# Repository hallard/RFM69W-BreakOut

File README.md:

RFM69W RFM69HW breakout board NRF24L01 socket
=============================================

This is a utility breakout board for connecting RFM69W or RFM69HW modules

this breakout add the feature of one of : 
- **adding** Micro SD card connector
- **adding** SPI Flash EEProm
- **adding** Some Leds to see what's going on

The same breakout board exists also for RFM12B and RFM69CW on this [repo][2]

This has been created to work with the [ArduiPi][4] Project, but this breakout
can be used anywhere where you use NRF24L01 or has NRF24L01 connector.

ArduiPi project is a shield for Raspberry Pi that brings Arduino low level extended I/O to Raspberry Pi.

You can find information about this project and others on [ArduiPi Site][4] 

Check out news and other on my [blog][5]

Detailed Description
====================

Everything is documented on this dedicated [post][6]

**Schematic**  

**Boards**  

&nbsp;
&nbsp;

[2]: [https://github.com/hallard/RFM12B-BreakOut]
[3]: http://hallard.me/rfm12b-breakout/ 
[4]: http://hallard.me/arduipi
[5]: http://hallard.me
[6]: http://hallard.me/rfm12b-breakout/

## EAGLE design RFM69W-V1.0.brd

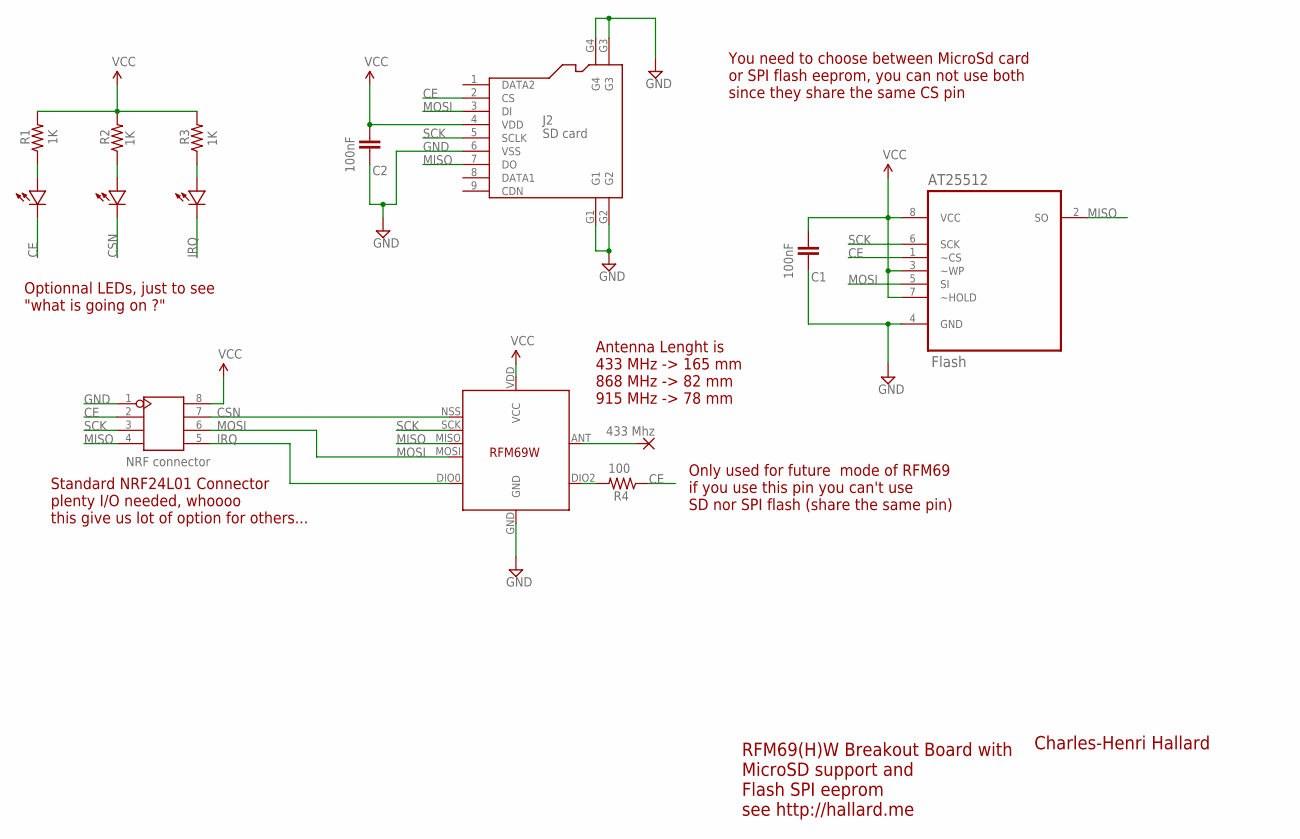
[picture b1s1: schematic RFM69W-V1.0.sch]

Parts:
ANT.: 433 Mhz; 1,6/0,8
AT25512: Flash; SOIC127P600X175-8N
C1, C2: 100nF; 0805-CAP
J1: NRF connector; 2X4P-2.54
J2: SD card; 9P-SMD-W/-RING
R1, R2, R3: 1K; 0805-RES
R4: 100; 0805-RES
U$1: RFM69; RFM69W-MINPADS
U$2, U$3, U$4: LED0805-LARGE; 0805-LED-LARGEPADS

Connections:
CE: AT25512.1 (~CS), J1.2, J2.2 (CS), R4.1, U$2.MINUS
CSN: J1.7, U$1.NSS (SEL), U$3.MINUS
GND: AT25512.4 (GND), C1.2, C2.2, J1.1, J2.6 (VSS), J2.G1, J2.G2, J2.G3, J2.G4, U$1.GND
IRQ: J1.5, U$1.DIO0, U$4.MINUS
MISO: AT25512.2 (SO), J1.4, J2.7 (DO), U$1.MISO
MOSI: AT25512.5 (SI), J1.6, J2.3 (DI), U$1.MOSI
unnamed: ANT..1, U$1.ANT
unnamed: R1.1, U$2.PLUS
unnamed: R2.1, U$3.PLUS
unnamed: R3.1, U$4.PLUS
unnamed: R4.2, U$1.DIO2
SCK: AT25512.6 (SCK), J1.3, J2.5 (SCLK), U$1.SCK
VCC: AT25512.3 (~WP), AT25512.7 (~HOLD), AT25512.8 (VCC), C1.1, C2.1, J1.8, J2.4 (VDD), R1.2, R2.2, R3.2, U$1.VDD (VCC)

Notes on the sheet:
You need to choose between MicroSd card or SPI flash eeprom, you can not use both since they share the same CS pin
Optionnal LEDs, just to see "what is going on ?"
Standard NRF24L01 Connector plenty I/O needed, whoooo this give us lot of option for others...
Antenna Lenght is 433 MHz -> 165 mm 868 MHz -> 82 mm 915 MHz -> 78 mm
RFM69(H)W Breakout Board with MicroSD support and Flash SPI eeprom see http://hallard.me
Charles-Henri Hallard
Only used for future mode of RFM69 if you use this pin you can't use SD nor SPI flash (share the same pin)

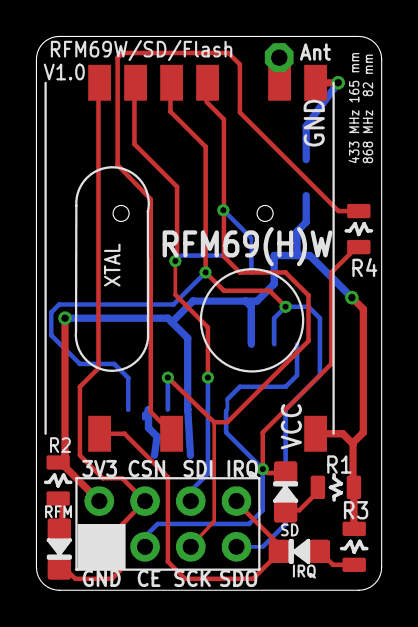
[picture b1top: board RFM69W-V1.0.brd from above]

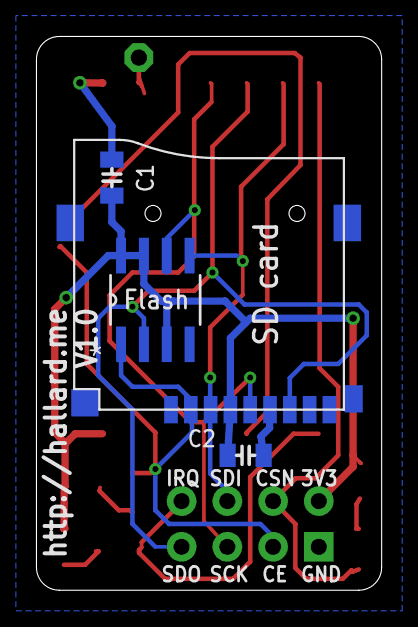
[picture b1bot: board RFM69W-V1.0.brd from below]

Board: 2 copper layers, 19.2 x 30.8 mm, 14 parts (4 on the bottom side), 13 nets.

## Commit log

2014-02-05 Cosmetic Change
2014-02-07 Removed Eagle Backup Files
2014-09-25 Cosmetic update
